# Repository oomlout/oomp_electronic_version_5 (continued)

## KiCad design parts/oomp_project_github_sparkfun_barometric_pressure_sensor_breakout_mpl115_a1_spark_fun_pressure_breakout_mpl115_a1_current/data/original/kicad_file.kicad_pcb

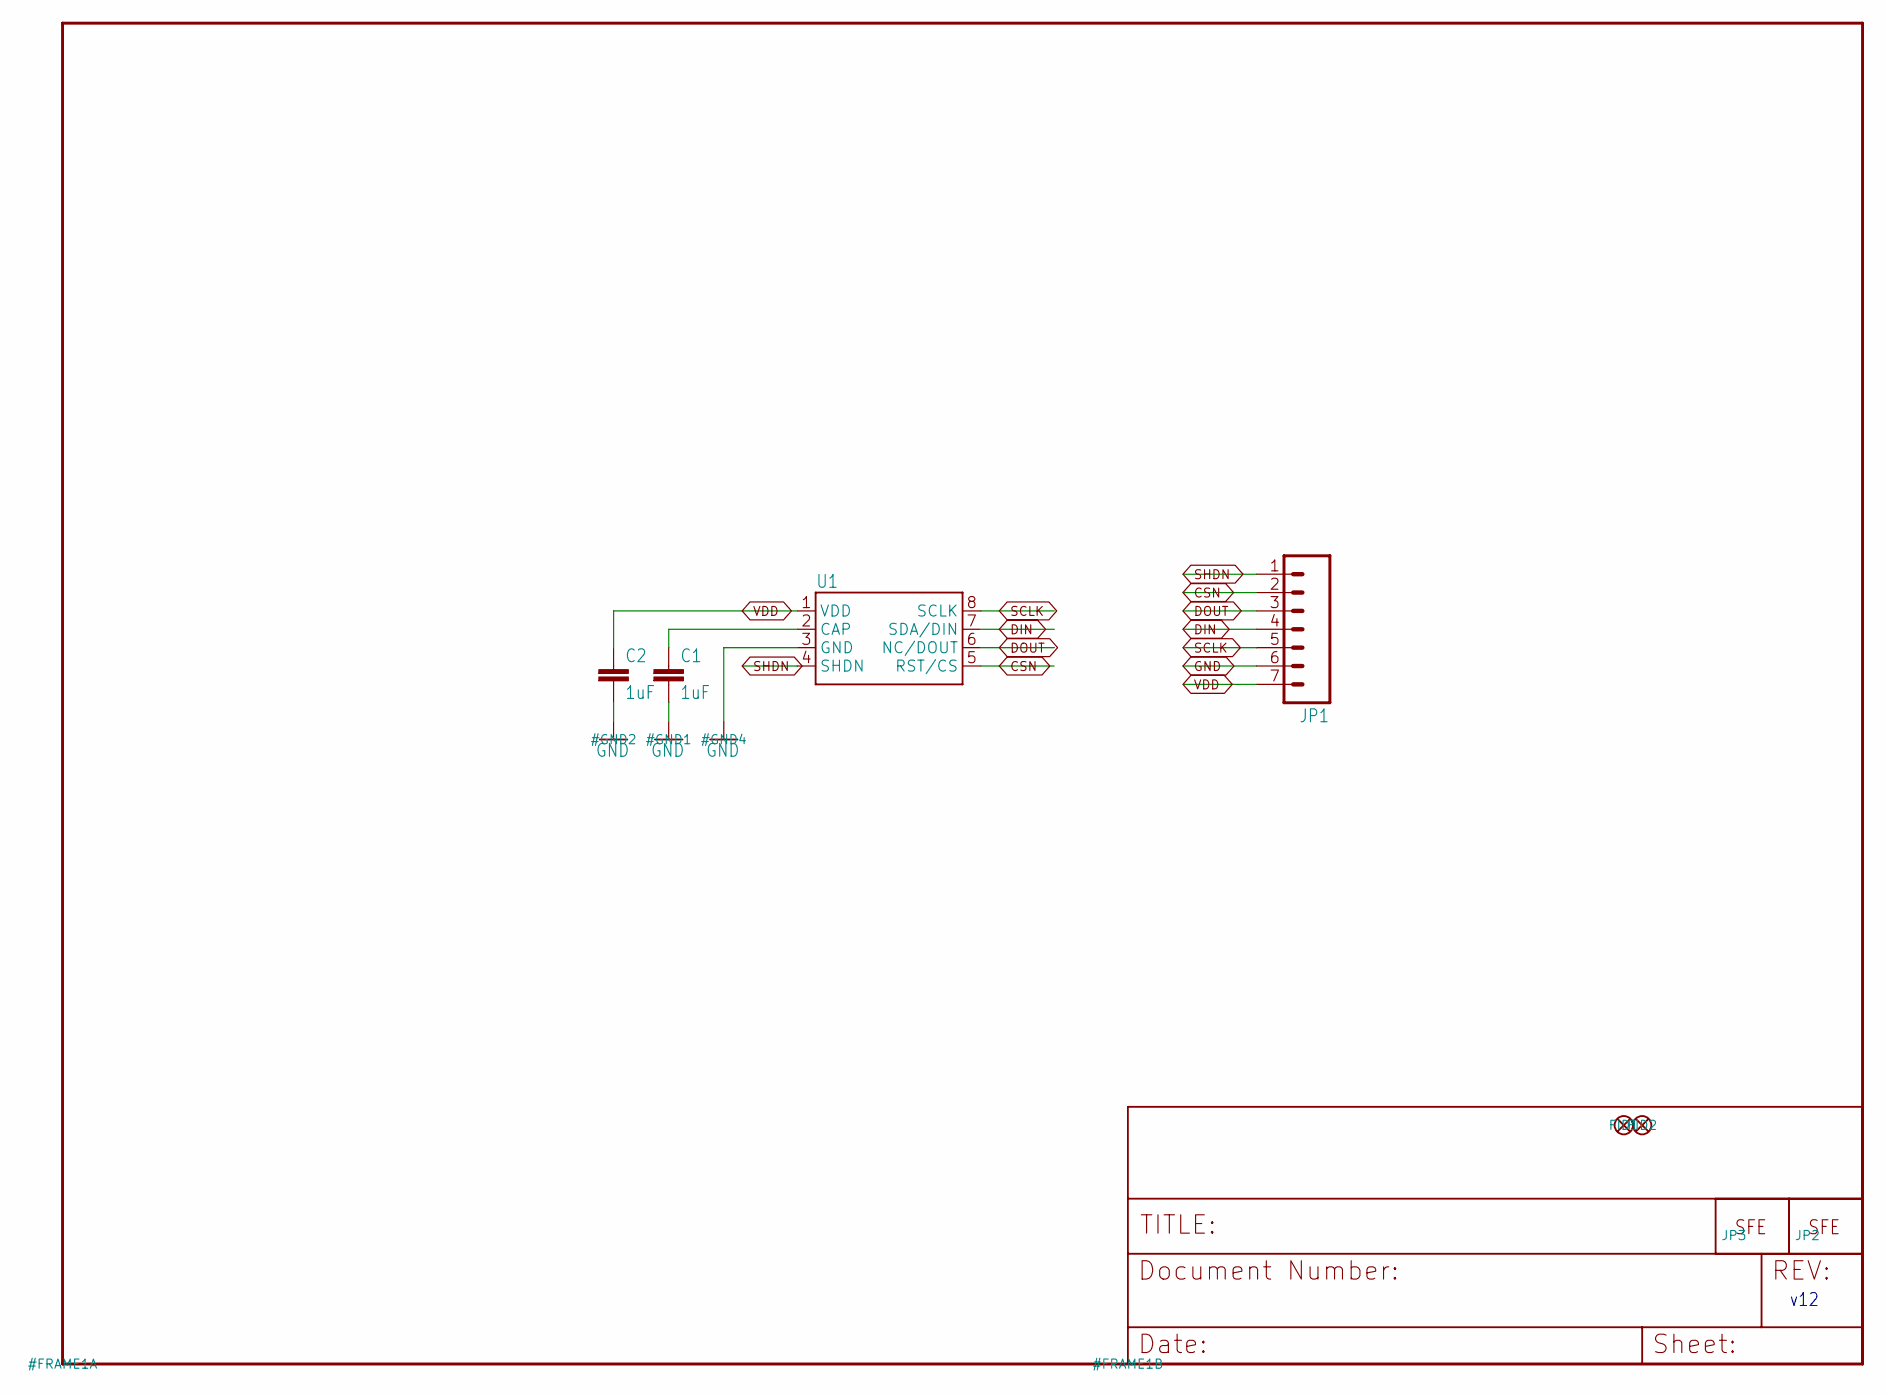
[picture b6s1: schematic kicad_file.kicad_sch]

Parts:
C1, C2: 1uF; 0603-CAP
FID1, FID2: FIDUCIALUFIDUCIAL; MICRO-FIDUCIAL
JP1: M07; 1X07
JP2: LOGO-SFESK; SFE-LOGO-FLAME
JP3: LOGO-SFENW2; SFE-NEW-WEB
U1: MPL115A; LGA8

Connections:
CAP: C1.1, U1.2 (CAP)
CSN: JP1.2, U1.5 (RST/CS)
DIN: JP1.4, U1.7 (SDA/DIN)
DOUT: JP1.3, U1.6 (NC/DOUT)
GND: C1.2, C2.2, JP1.6, U1.3 (GND)
SCLK: JP1.5, U1.8 (SCLK)
SHDN: JP1.1, U1.4 (SHDN)
VDD: C2.1, JP1.7, U1.1 (VDD)

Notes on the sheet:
v12

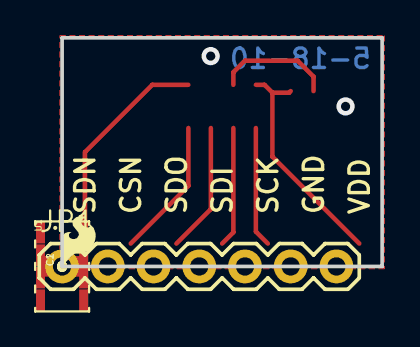
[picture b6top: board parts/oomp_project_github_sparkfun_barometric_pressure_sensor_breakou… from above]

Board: 2 copper layers, 17.8 x 12.7 mm, 8 parts (1 on the bottom side), 8 nets.

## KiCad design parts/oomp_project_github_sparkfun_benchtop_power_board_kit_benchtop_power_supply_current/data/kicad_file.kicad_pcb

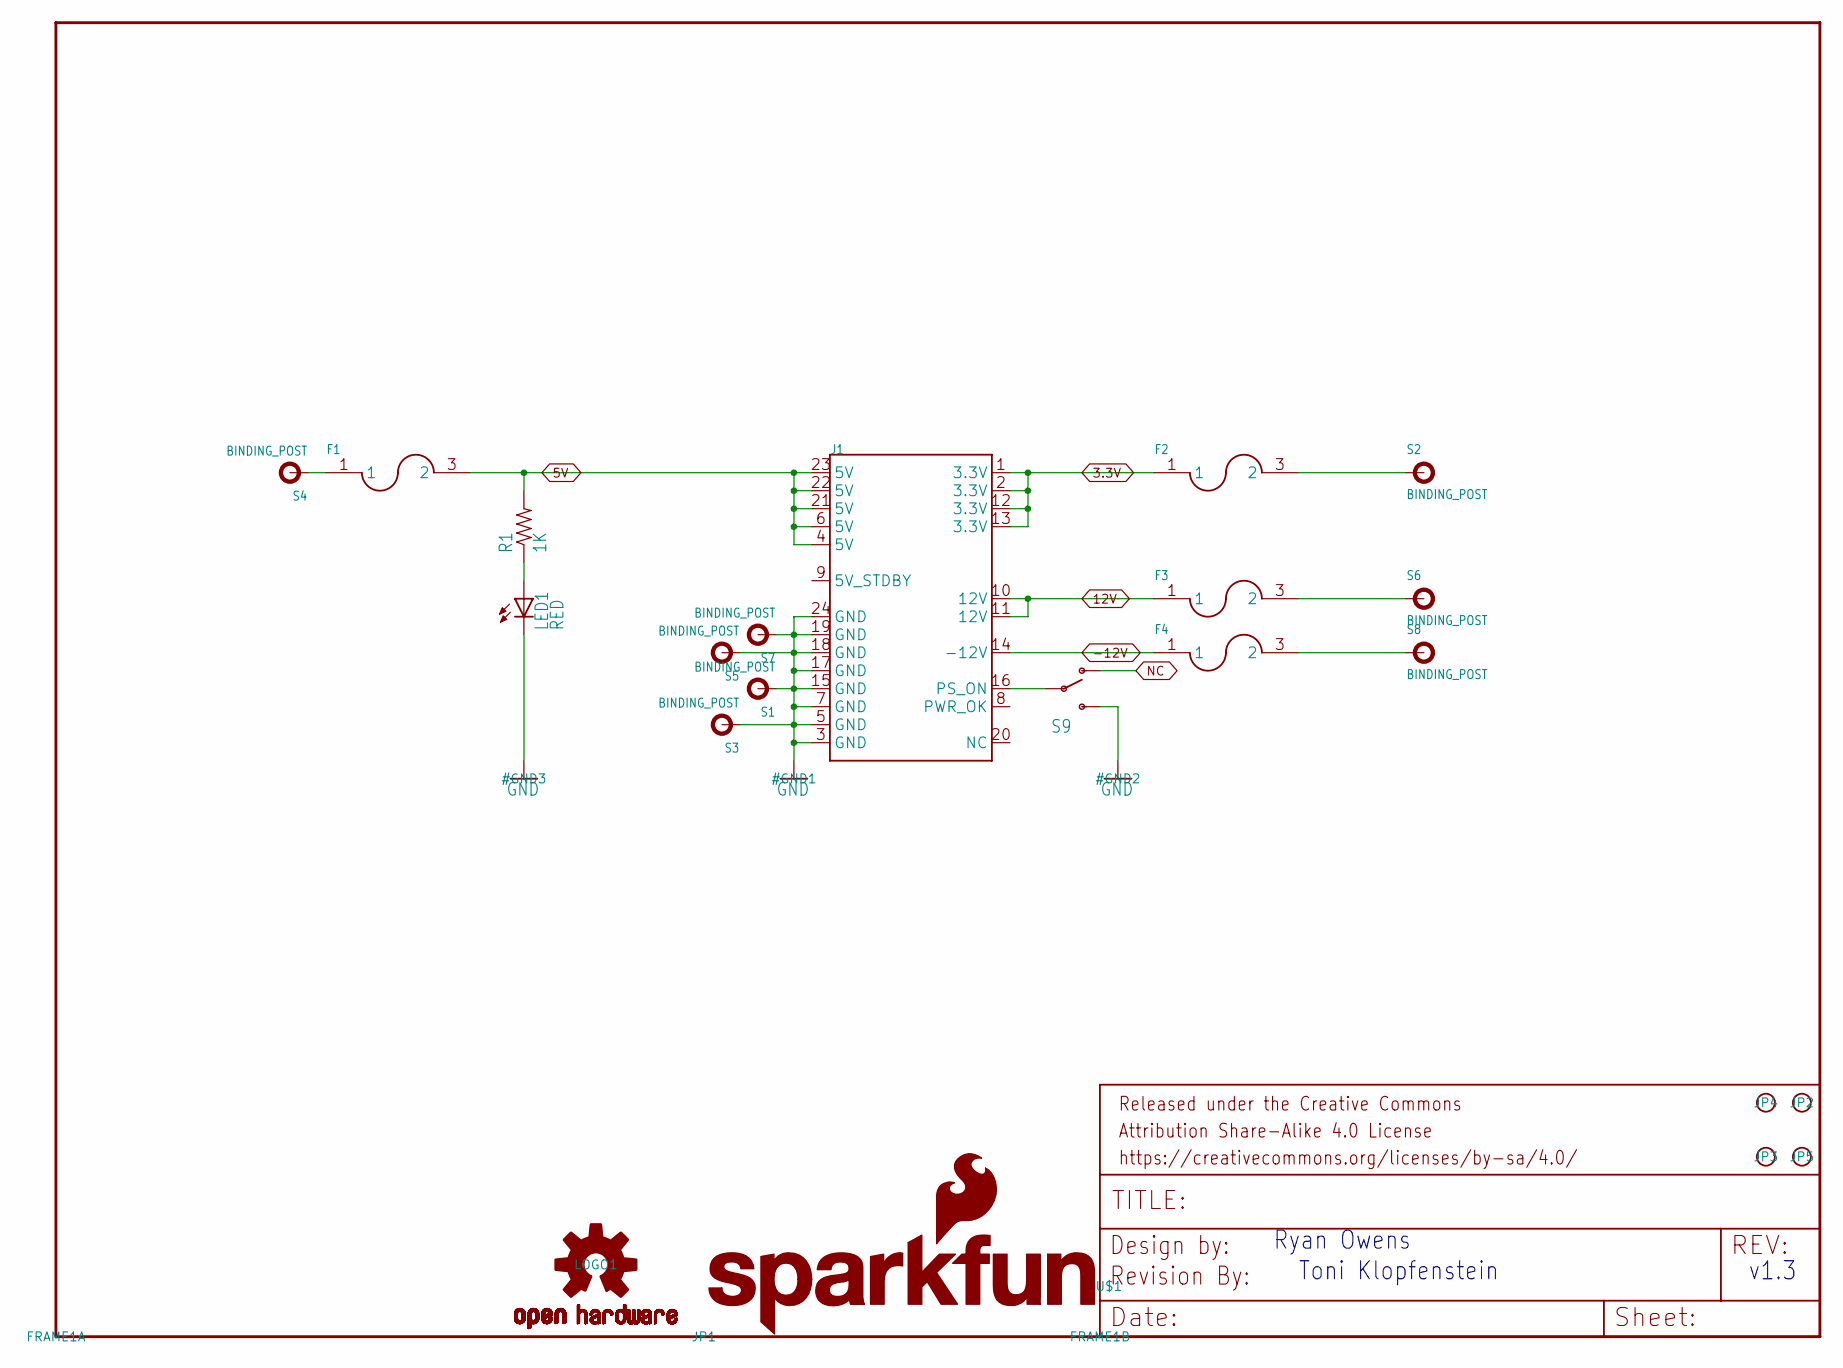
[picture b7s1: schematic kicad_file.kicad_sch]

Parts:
F1, F2, F3, F4: FUSEX20MM; FUSE_5MM
FRAME1: FRAME-LETTER; CREATIVE_COMMONS
J1: ATX24RH; ATX24_RIGHT_ANGLE
JP1: SFE_LOGO_NAME_FLAME.3_INCH; SFE_LOGO_NAME_FLAME_.3
JP2, JP3, JP4, JP5: STAND-OFF
LED1: RED; LED5MM
LOGO1: OSHW-LOGOL; OSHW-LOGO-L
R1: 1K; AXIAL-0.3
S1, S2, S3, S4, S5, S6, S7, S8: BINDING_POST
S9: SWITCH-SPDTKIT; SWITCH-SPDT_KIT
U$1: REVISION

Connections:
3.3V: F2.1, J1.1 (3.3V), J1.2 (3.3V), J1.12 (3.3V), J1.13 (3.3V)
3.3V_P: F2.3 (2), S2.P$1
5V: F1.3 (2), J1.4 (5V), J1.6 (5V), J1.21 (5V), J1.22 (5V), J1.23 (5V), R1.P$2 (2)
5V_P: F1.1, S4.P$1
12V: F3.1, J1.10 (12V), J1.11 (12V)
12V_P: F3.3 (2), S6.P$1
-12V: F4.1, J1.14 (-12V)
-12V_P: F4.3 (2), S8.P$1
GND: J1.3 (GND), J1.5 (GND), J1.7 (GND), J1.15 (GND), J1.17 (GND), J1.18 (GND), J1.19 (GND), J1.24 (GND), LED1.K (C), S1.P$1, S3.P$1, S5.P$1, S7.P$1, S9.3 (S)
unnamed: LED1.A, R1.P$1 (1)
unnamed: J1.16 (PS_ON), S9.2
NC: S9.1 (O)

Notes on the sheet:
Toni Klopfenstein
v1.3
Ryan Owens

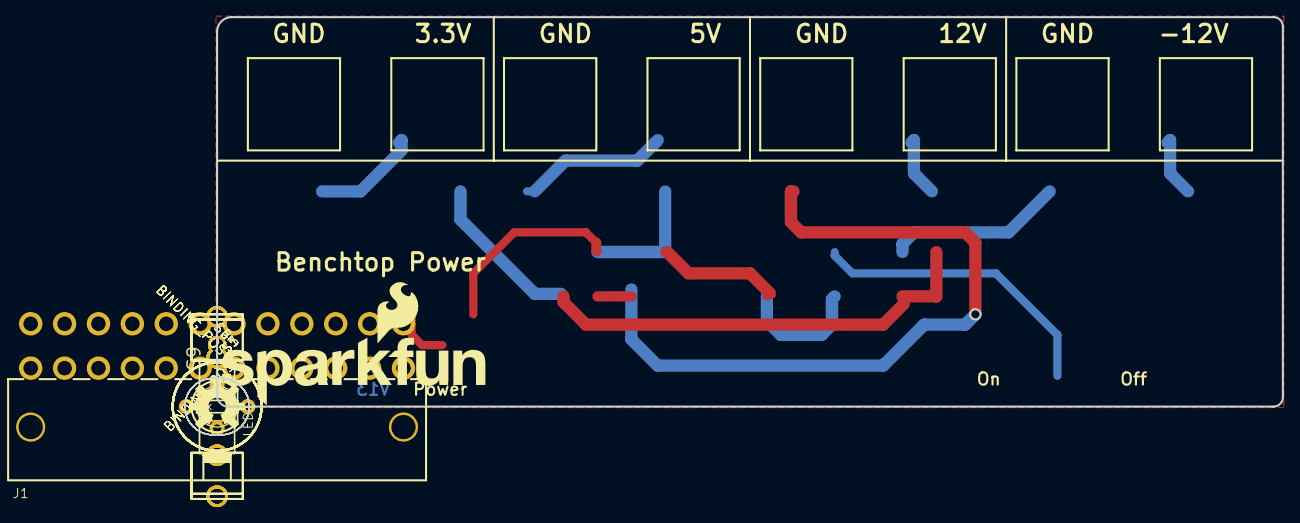
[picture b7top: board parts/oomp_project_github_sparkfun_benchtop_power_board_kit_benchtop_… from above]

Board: 2 copper layers, 136.1 x 51.8 mm, 24 parts (0 on the bottom side), 11 nets.

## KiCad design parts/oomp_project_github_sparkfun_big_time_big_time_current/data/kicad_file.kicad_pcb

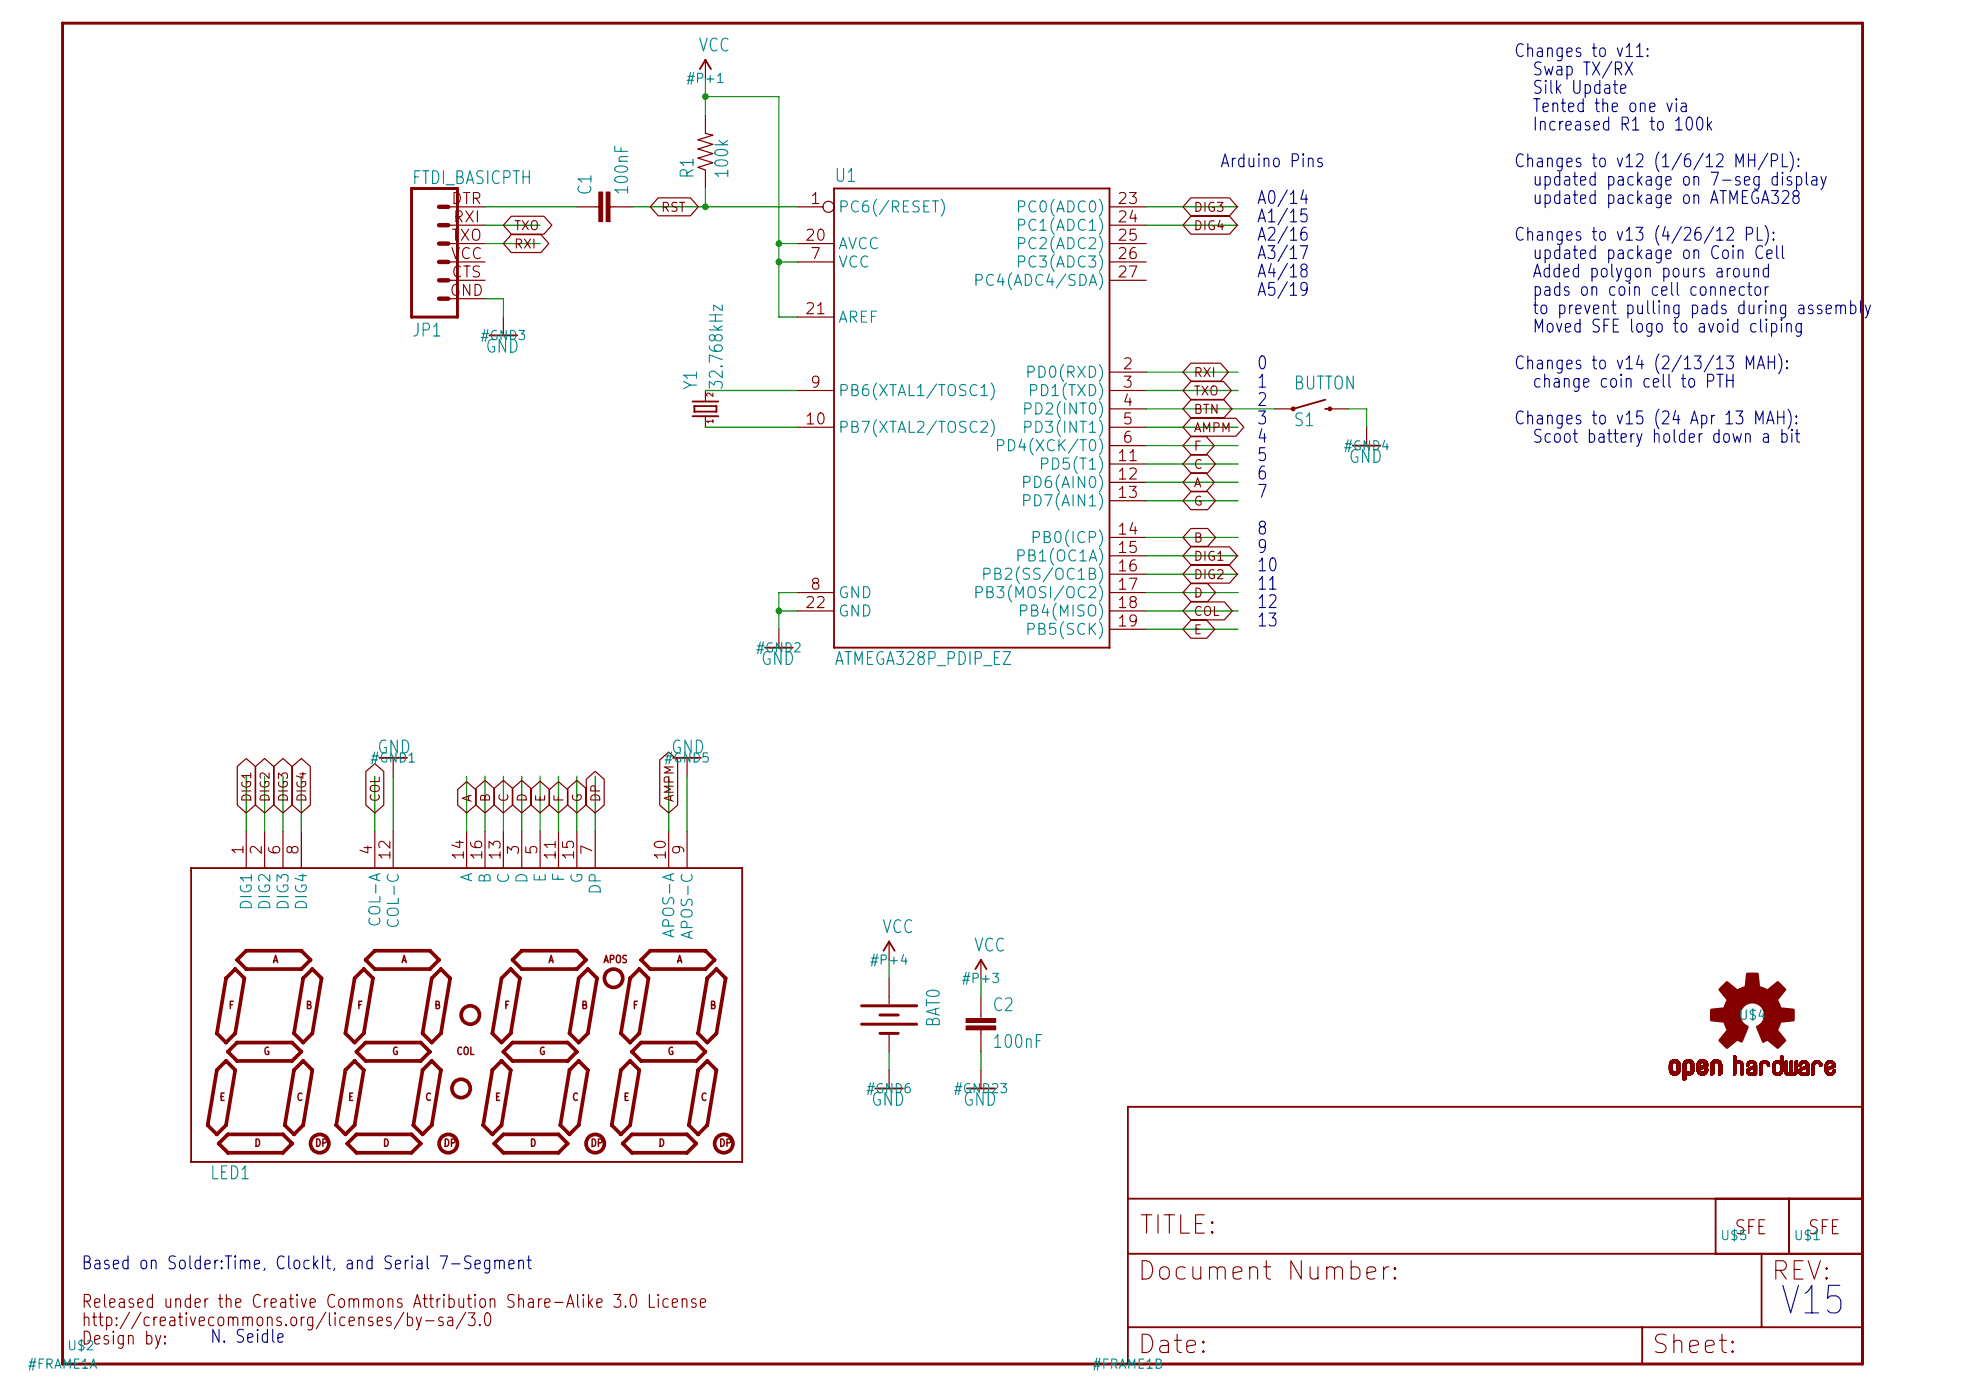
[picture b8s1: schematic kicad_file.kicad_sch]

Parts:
BAT0: BATTERYFOB; BATTERY_20MM_PTH_COMPACT
C1, C2: 100nF; CAP-PTH-SMALLEZ
JP1: FTDI_BASICPTH; FTDI_BASIC
LED1: 7-SEGMENT-4DIGIT-YOUNGSUNKIT; 7-SEGMENT-4DIGIT-YOUNGSUN-KIT
R1: 100k; AXIAL-0.3-KIT
S1: BUTTON; TACTILE-PTH-SIDEEZ
U1: ATMEGA328P_PDIP_EZ; DIL28-EZ
U$1: LOGO-SFESK; SFE-LOGO-FLAME
U$2: CREATIVE_COMMONS
U$4: OSHW-LOGOS; OSHW-LOGO-S
U$5: LOGO-SFENW2; SFE-NEW-WEB
Y1: 32.768kHz; TC26HEZ

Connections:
A: LED1.14 (A), U1.12 (PD6(AIN0))
AMPM: LED1.10 (APOS-A), U1.5 (PD3(INT1))
B: LED1.16 (B), U1.14 (PB0(ICP))
BTN: S1.1, U1.4 (PD2(INT0))
C: LED1.13 (C), U1.11 (PD5(T1))
COL: LED1.4 (COL-A), U1.18 (PB4(MISO))
D: LED1.3 (D), U1.17 (PB3(MOSI/OC2))
DIG1: LED1.1 (DIG1), U1.15 (PB1(OC1A))
DIG2: LED1.2 (DIG2), U1.16 (PB2(SS/OC1B))
DIG3: LED1.6 (DIG3), U1.23 (PC0(ADC0))
DIG4: LED1.8 (DIG4), U1.24 (PC1(ADC1))
DP: LED1.7 (DP)
E: LED1.5 (E), U1.19 (PB5(SCK))
F: LED1.11 (F), U1.6 (PD4(XCK/T0))
G: LED1.15 (G), U1.13 (PD7(AIN1))
GND: BAT0.2 (-), C2.2, JP1.GND (6), LED1.9 (APOS-C), LED1.12 (COL-C), S1.2, U1.8 (GND), U1.22 (GND)
unnamed: U1.10 (PB7(XTAL2/TOSC2)), Y1.1
unnamed: U1.9 (PB6(XTAL1/TOSC1)), Y1.2
unnamed: C1.1, JP1.DTR (1)
RST: C1.2, R1.P$1 (1), U1.1 (PC6(/RESET))
RXI: JP1.TXO (3), U1.2 (PD0(RXD))
TXO: JP1.RXI (2), U1.3 (PD1(TXD))
VCC: BAT0.1 (+), C2.1, R1.P$2 (2), U1.7 (VCC), U1.20 (AVCC), U1.21 (AREF)

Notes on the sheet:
updated package on ATMEGA328
A0/14
Arduino Pins
Changes to v14 (2/13/13 MAH):
updated package on Coin Cell
V15
Changes to v13 (4/26/12 PL):
Swap TX/RX
Changes to v11:
N. Seidle
Silk Update
Moved SFE logo to avoid cliping
to prevent pulling pads during assembly
Changes to v12 (1/6/12 MH/PL):
Scoot battery holder down a bit
A5/19
pads on coin cell connector
Changes to v15 (24 Apr 13 MAH):
A4/18
updated package on 7-seg display
Based on Solder:Time, ClockIt, and Serial 7-Segment
A2/16
Tented the one via
A1/15
change coin cell to PTH
Increased R1 to 100k
A3/17
Added polygon pours around

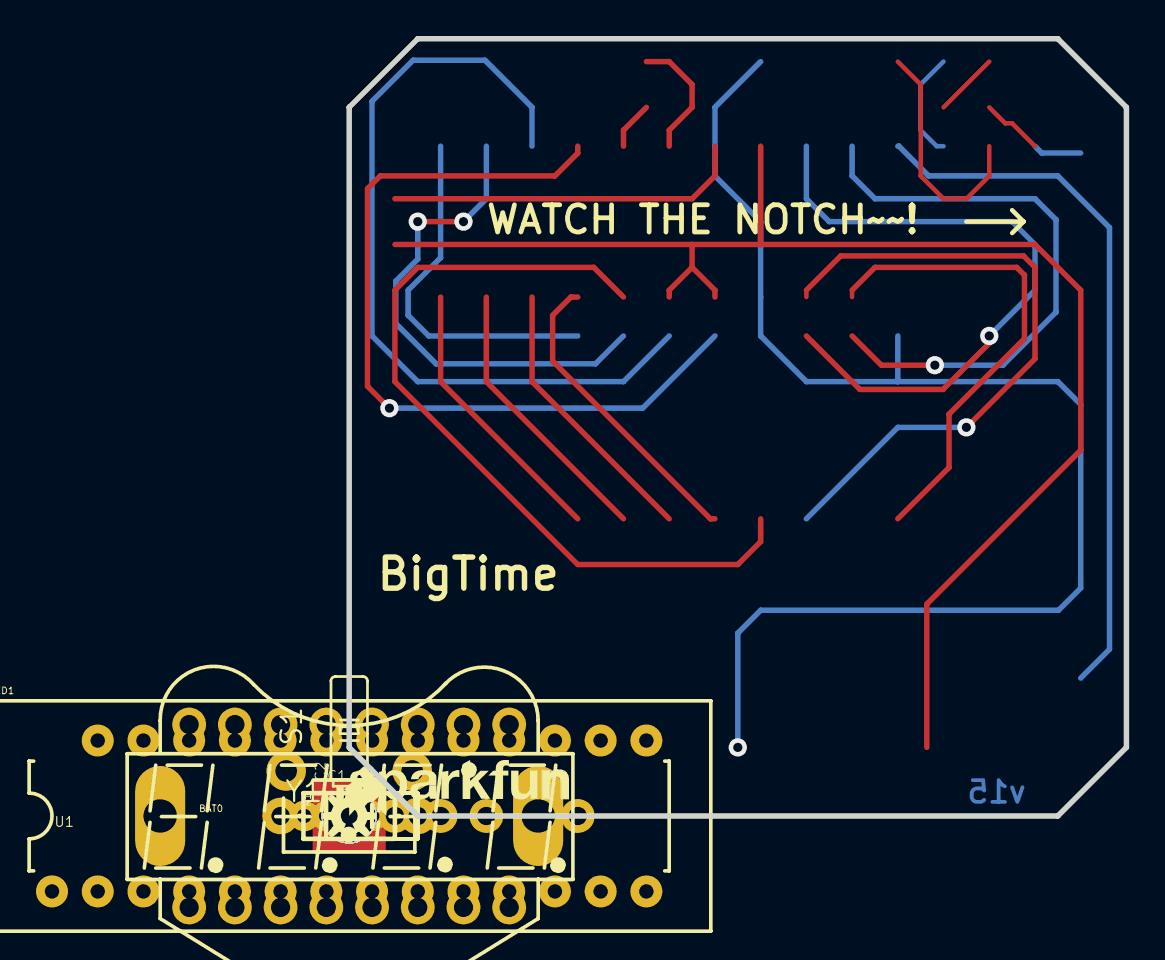
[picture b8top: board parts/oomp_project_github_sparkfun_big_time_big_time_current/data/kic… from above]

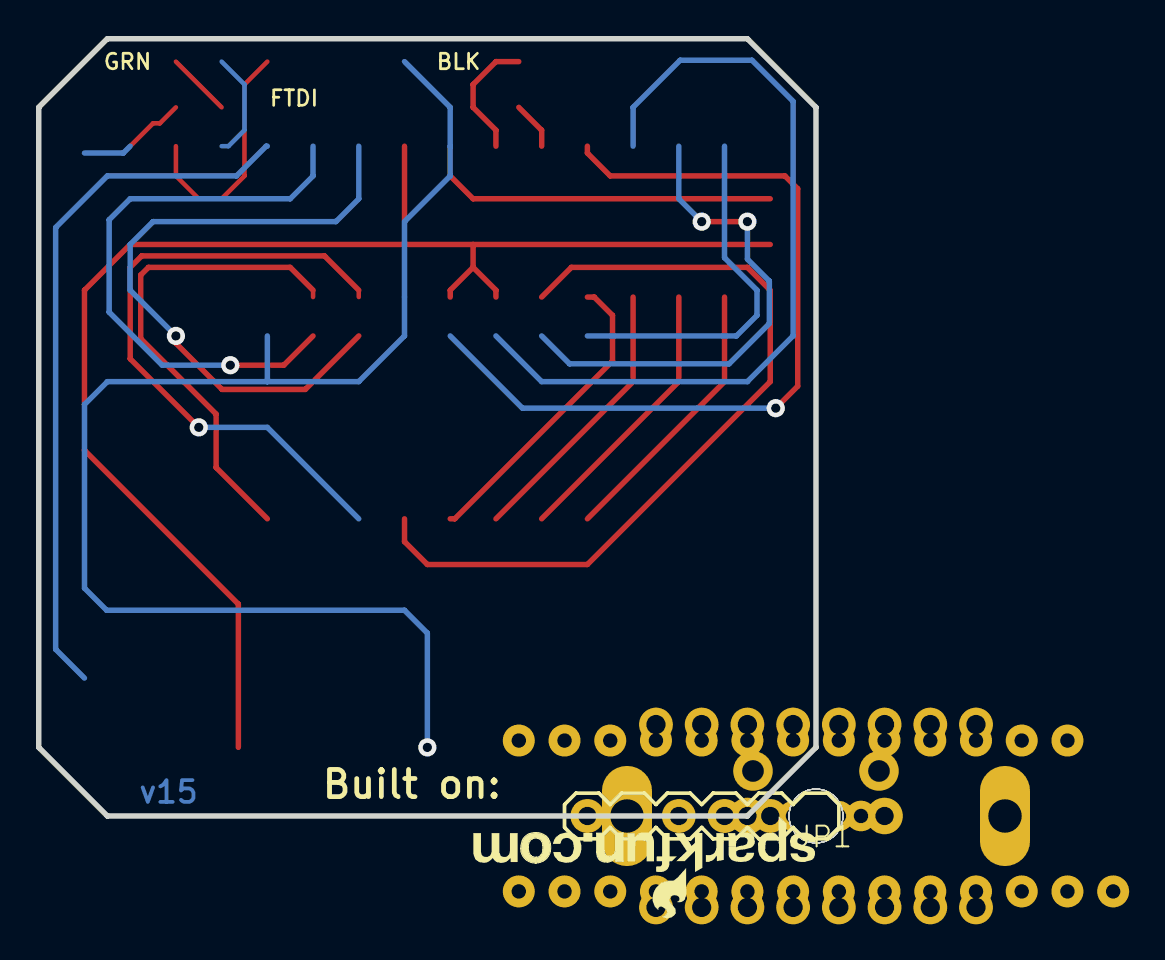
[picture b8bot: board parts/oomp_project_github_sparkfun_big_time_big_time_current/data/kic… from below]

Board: 4 copper layers, 43.2 x 43.2 mm, 18 parts (2 on the bottom side), 22 nets.

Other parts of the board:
U$3: LOGO-SFENEW; SFE-NEW-WEBLOGO
UNK_HOLE_0: dummyfp0
UNK_HOLE_1: dummyfp1
UNK_HOLE_2: dummyfp2
UNK_HOLE_3: dummyfp3
